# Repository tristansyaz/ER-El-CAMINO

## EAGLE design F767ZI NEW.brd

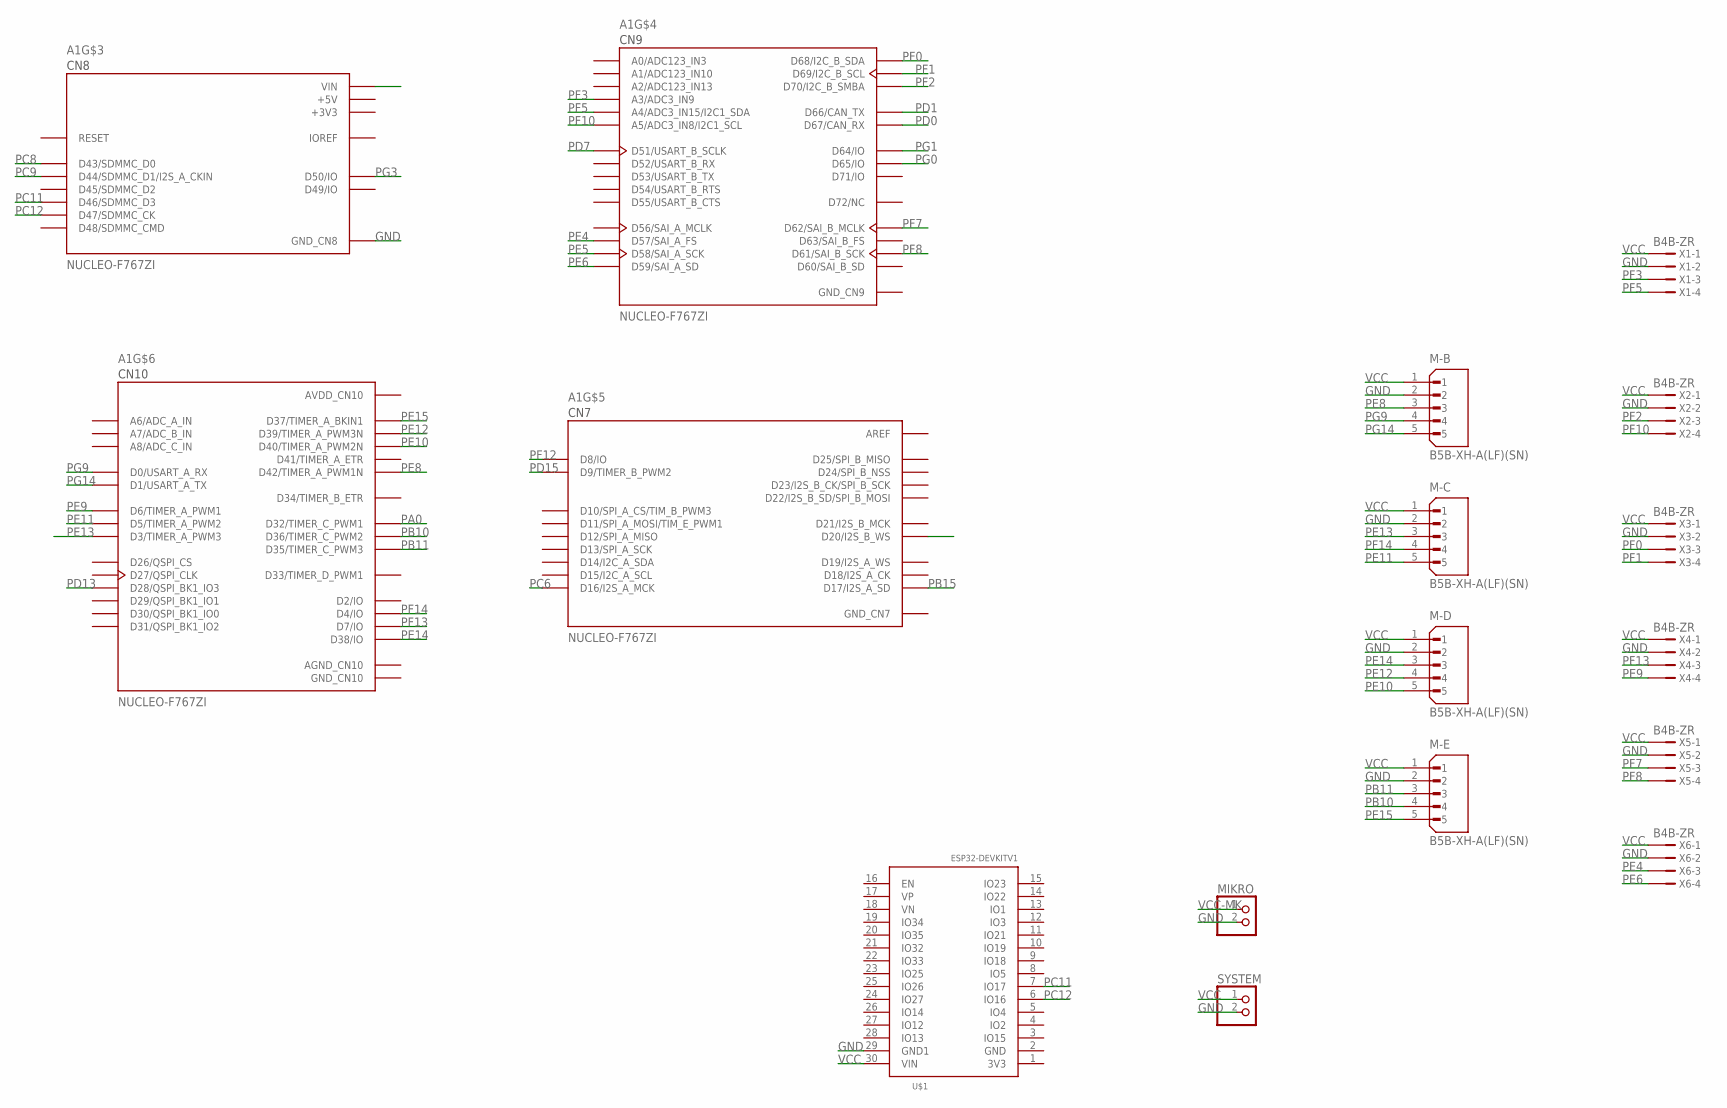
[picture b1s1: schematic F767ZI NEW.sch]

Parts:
A1: NUCLEO-F767ZI; ST_NUCLEO-F767ZI
M-B: B5B-XH-A(LF)(SN); JST_B5B-XH-A(LF)(SN)
M-C: B5B-XH-A(LF)(SN); JST_B5B-XH-A(LF)(SN)
M-D: B5B-XH-A(LF)(SN); JST_B5B-XH-A(LF)(SN)
M-E: B5B-XH-A(LF)(SN); JST_B5B-XH-A(LF)(SN)
MIKRO: PINHD-1X2; 1X02
SYSTEM: PINHD-1X2; 1X02
U$1: ESP32DEVKITV1; ESP32-DEVKITV1
X1, X2, X3, X4, X5, X6: B4B-ZR

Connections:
+3V3: A1.CN8_7 (+3V3)
+5V: A1.CN8_9 (+5V)
AGND_CN10: A1.CN10_3 (AGND_CN10)
AREF: A1.CN7_6 (AREF)
AVDD_CN10: A1.CN10_1 (AVDD_CN10)
GND: A1.CN8_11 (GND_CN8), A1.CN8_13 (GND_CN8), M-B.2, M-C.2, M-D.2, M-E.2, MIKRO.2, SYSTEM.2, U$1.29 (GND1), X1.2, X2.2, X3.2, X4.2, X5.2, X6.2
GND_CN7: A1.CN7_8 (GND_CN7)
GND_CN9: A1.CN9_12 (GND_CN9), A1.CN9_23 (GND_CN9)
GND_CN10: A1.CN10_5 (GND_CN10), A1.CN10_17 (GND_CN10), A1.CN10_22 (GND_CN10), A1.CN10_27 (GND_CN10)
PA0: A1.CN10_29 (D32/TIMER_C_PWM1)
PA15: A1.CN7_9 (D20/I2S_B_WS)
PB10: A1.CN10_32 (D36/TIMER_C_PWM2), M-E.4
PB11: A1.CN10_34 (D35/TIMER_C_PWM3), M-E.3
PB15: A1.CN7_3 (D17/I2S_A_SD)
PC6: A1.CN7_1 (D16/I2S_A_MCK)
PC8: A1.CN8_2 (D43/SDMMC_D0)
PC9: A1.CN8_4 (D44/SDMMC_D1/I2S_A_CKIN)
PC11: A1.CN8_8 (D46/SDMMC_D3), U$1.7 (IO17)
PC12: A1.CN8_10 (D47/SDMMC_CK), U$1.6 (IO16)
PD0: A1.CN9_25 (D67/CAN_RX)
PD1: A1.CN9_27 (D66/CAN_TX)
PD7: A1.CN9_2 (D51/USART_B_SCLK)
PD13: A1.CN10_19 (D28/QSPI_BK1_IO3)
PD15: A1.CN7_18 (D9/TIMER_B_PWM2)
PE4: A1.CN9_16 (D57/SAI_A_FS), X6.3
PE5: A1.CN9_18 (D58/SAI_A_SCK)
PE6: A1.CN9_20 (D59/SAI_A_SD), X6.4
PE8: A1.CN10_18 (D42/TIMER_A_PWM1N), M-B.3
PE9: A1.CN10_4 (D6/TIMER_A_PWM1), X4.4
PE10: A1.CN10_24 (D40/TIMER_A_PWM2N), M-D.5
PE11: A1.CN10_6 (D5/TIMER_A_PWM2), M-C.5
PE12: A1.CN10_26 (D39/TIMER_A_PWM3N), M-D.4
PE13: A1.CN10_10 (D3/TIMER_A_PWM3), M-C.3
PE14: A1.CN10_28 (D38/IO), M-D.3
PE15: A1.CN10_30 (D37/TIMER_A_BKIN1), M-E.5
PF0: A1.CN9_21 (D68/I2C_B_SDA), X3.3
PF1: A1.CN9_19 (D69/I2C_B_SCL), X3.4
PF2: A1.CN9_17 (D70/I2C_B_SMBA), X2.3
PF3: A1.CN9_7 (A3/ADC3_IN9), X1.3
PF5: A1.CN9_9 (A4/ADC3_IN15/I2C1_SDA), X1.4
PF7: A1.CN9_26 (D62/SAI_B_MCLK), X5.3
PF8: A1.CN9_24 (D61/SAI_B_SCK), X5.4
PF10: A1.CN9_11 (A5/ADC3_IN8/I2C1_SCL), X2.4
PF12: A1.CN7_20 (D8/IO)
PF13: A1.CN10_2 (D7/IO), X4.3
PF14: A1.CN10_8 (D4/IO), M-C.4
PG0: A1.CN9_29 (D65/IO)
PG1: A1.CN9_30 (D64/IO)
PG3: A1.CN8_16 (D50/IO)
PG9: A1.CN10_16 (D0/USART_A_RX), M-B.4
PG14: A1.CN10_14 (D1/USART_A_TX), M-B.5
VCC: M-B.1, M-C.1, M-D.1, M-E.1, SYSTEM.1, U$1.30 (VIN), X1.1, X2.1, X3.1, X4.1, X5.1, X6.1
VCC-MK: A1.CN8_15 (VIN), MIKRO.1

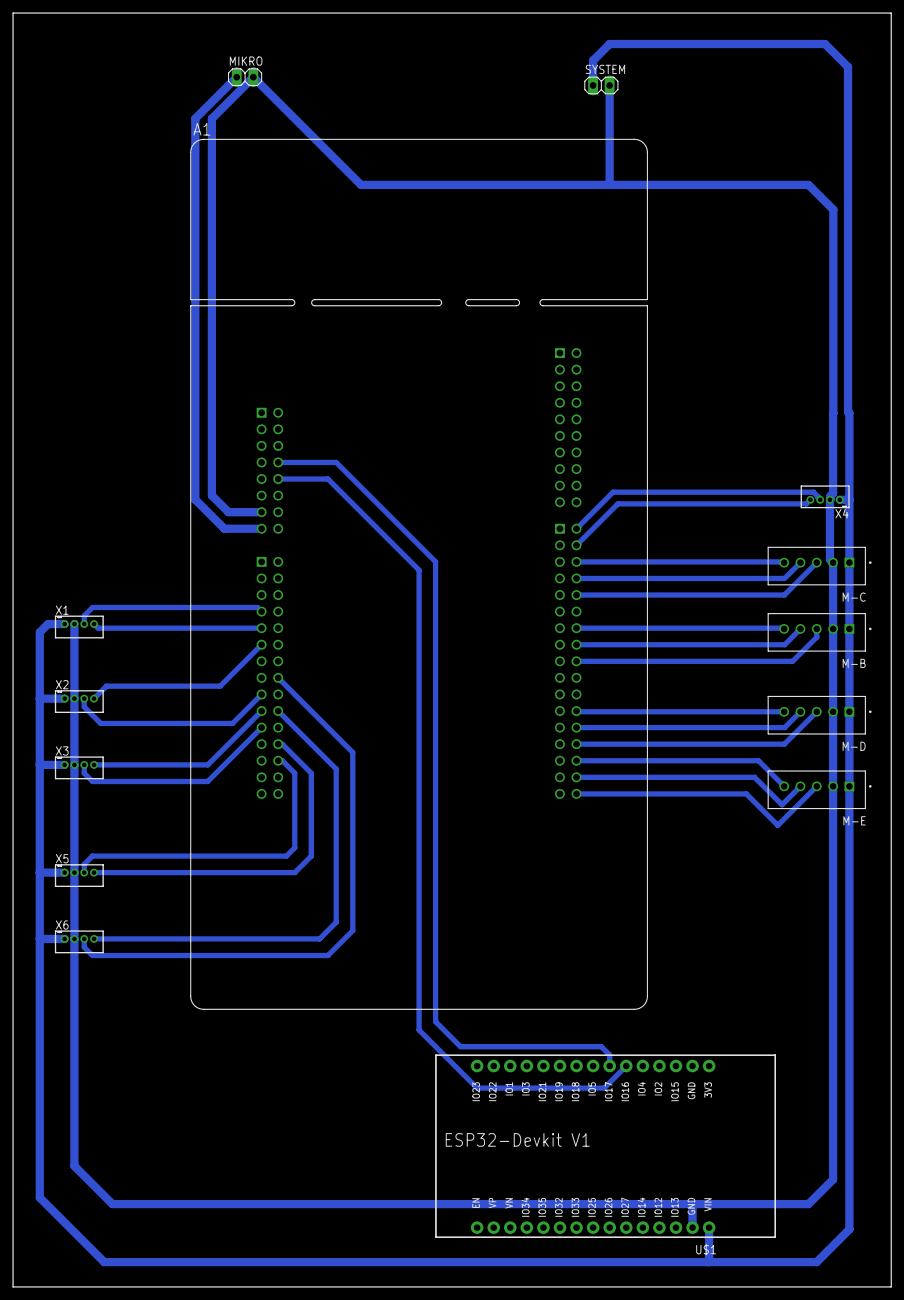
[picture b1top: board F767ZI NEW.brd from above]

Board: 2 copper layers, 134.6 x 195.2 mm, 14 parts (0 on the bottom side), 31 nets.

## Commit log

2023-03-13 Create ER
2023-03-13 add Gyro.ino
